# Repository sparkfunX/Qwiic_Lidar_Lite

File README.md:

SparkFun Qwiic LIDAR Lite v4
========================================

<table class="table table-hover table-striped table-bordered">
  <tr align="center">
   <td></td>
   <td></td>
  </tr>
  <tr align="center">
   <td><i>Qwiic LIDAR-Lite v4 [<a href="https://www.sparkfun.com/products/15777">SPX-15777</a>]</i></td>
   <td><i>Garmin LIDAR-Lite v4 LED - Distance Measurement Sensor [<a href="https://www.sparkfun.com/products/15776">SEN-15776</a>]</i></td>
  </tr>
</table>

Arduino library for GARMIN LIDAR Lite v4: high-performance optical distance sensing.

Repository Contents
-------------------

* **/examples** - Example sketches for the library (.ino). Run these from the Arduino IDE.
* **/src** - Source files for the library (.cpp, .h).
* **keywords.txt** - Keywords from this library that will be highlighted in the Arduino IDE. 
* **library.properties** - General library properties for the Arduino package manager. 

Documentation
--------------

* **[Installing an Arduino Library Guide](https://learn.sparkfun.com/tutorials/installing-an-arduino-library)** - Basic information on how to install an Arduino library.

License Information
-------------------

This product is _**open source**_!

Please review the LICENSE.md file for license information.

If you have any questions or concerns on licensing, please contact technical support on our [SparkFun forums](https://forum.sparkfun.com/viewforum.php?f=152).

Distributed as-is; no warranty is given.

- Your friends at SparkFun.

_<COLLABORATION CREDIT>_

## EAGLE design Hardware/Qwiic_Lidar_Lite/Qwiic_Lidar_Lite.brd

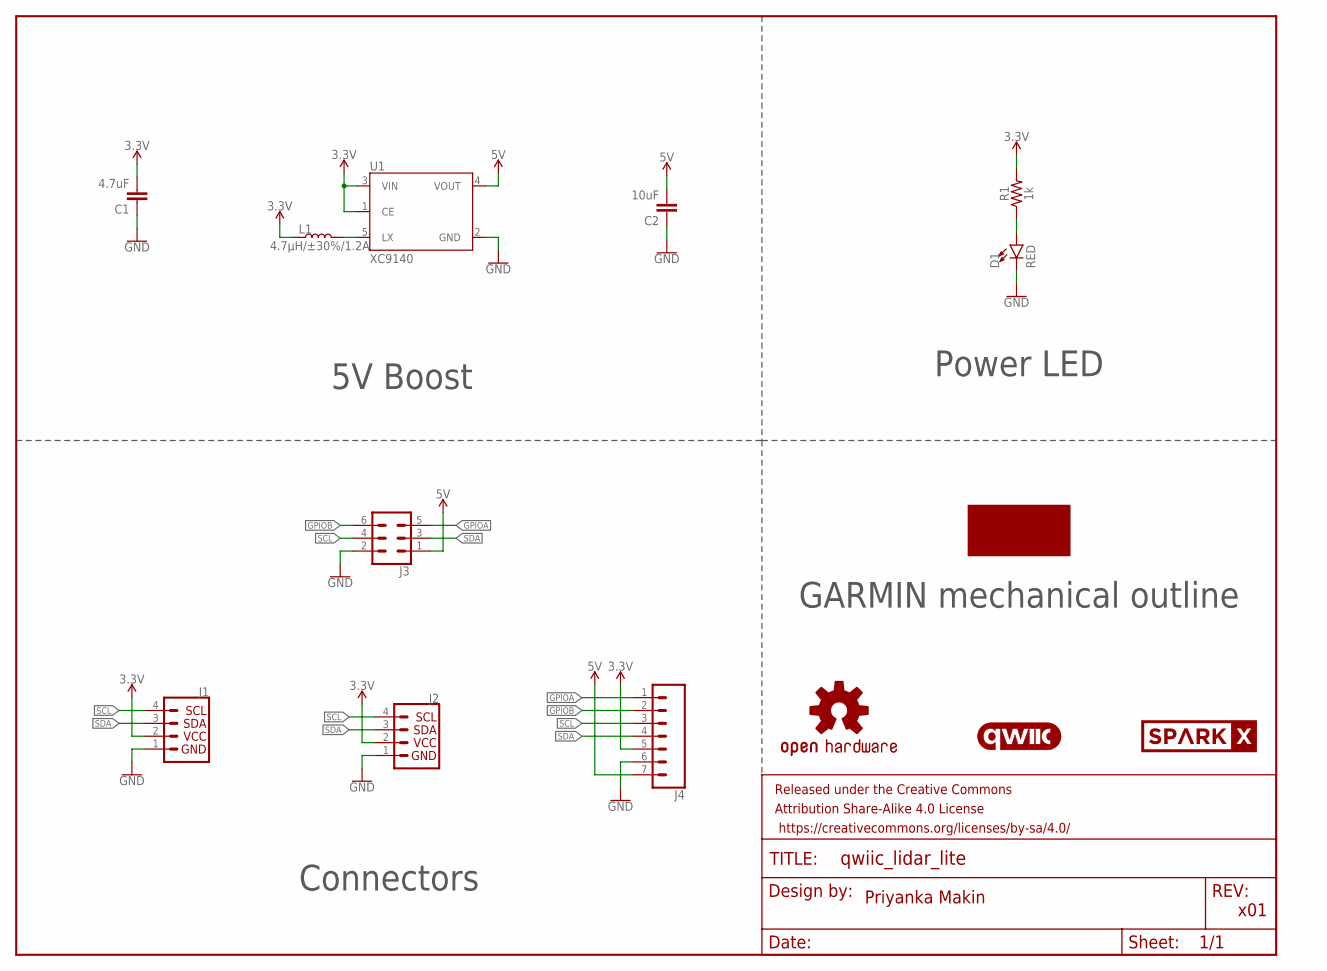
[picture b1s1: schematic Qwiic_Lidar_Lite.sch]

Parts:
C1: 4.7uF; 0603
C2: 10uF; 0603
D1: RED; LED-0603
FRAME1: FRAME-LETTER; CREATIVE_COMMONS
J1, J2: QWIIC_CONNECTORJS-1MM; JST04_1MM_RA
J3: CONN_03X22MM; CONN_3X2_2MM
J4: CONN_07NO_SILK; 1X07_NO_SILK
L1: 4.7µH/±30%/1.2A; INDUCTOR_4.7UH
LOGO1: QWIIC_LOGO_CONNECTOR; QWIIC_5.5MM
LOGO2: OSHW-LOGOMINI; OSHW-LOGO-MINI
R1: 1k; 0603
U1: XC9140; SOT23-5
U$7: LIDAR_LITE
U$8: SPARKX-LOGO4; SPARKX-MEDIUM

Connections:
3.3V: C1.2, J1.2, J2.2, J4.5, L1.P$1 (1), R1.2, U1.1 (CE), U1.3 (VIN)
5V: C2.2, J3.1, J4.7, U1.4 (VOUT)
GND: C1.1, C2.1, D1.C, J1.1, J2.1, J3.2, J4.6, U1.2 (GND)
GPIOA: J3.5, J4.1
GPIOB: J3.6, J4.2
unnamed: D1.A, R1.1
unnamed: L1.P$2 (2), U1.5 (LX)
SCL: J1.4, J2.4, J3.4, J4.3
SDA: J1.3, J2.3, J3.3, J4.4

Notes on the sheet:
Connectors
Priyanka Makin
x01
GARMIN mechanical outline
5V Boost
Power LED

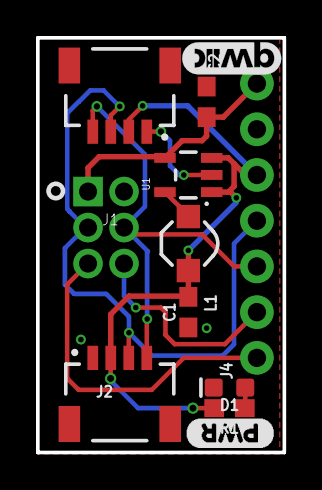
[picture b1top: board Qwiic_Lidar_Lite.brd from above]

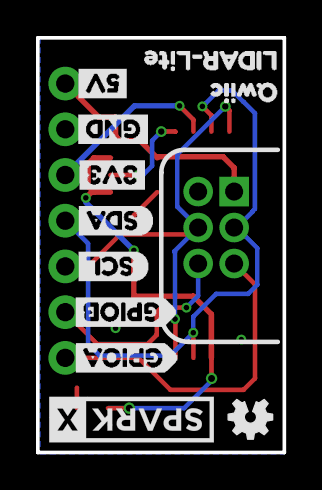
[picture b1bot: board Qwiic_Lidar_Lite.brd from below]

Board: 2 copper layers, 13.7 x 23.0 mm, 25 parts (13 on the bottom side), 9 nets.

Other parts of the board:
U$1: GND3
U$2: 3V30
U$3: GPIOA5
U$4: GPIOB2
U$5: SCL1
U$6: SDA4
U$9: QWIIC0
U$10: 5V0
U$11: LIDAR#LITE1
U$12: PWR0

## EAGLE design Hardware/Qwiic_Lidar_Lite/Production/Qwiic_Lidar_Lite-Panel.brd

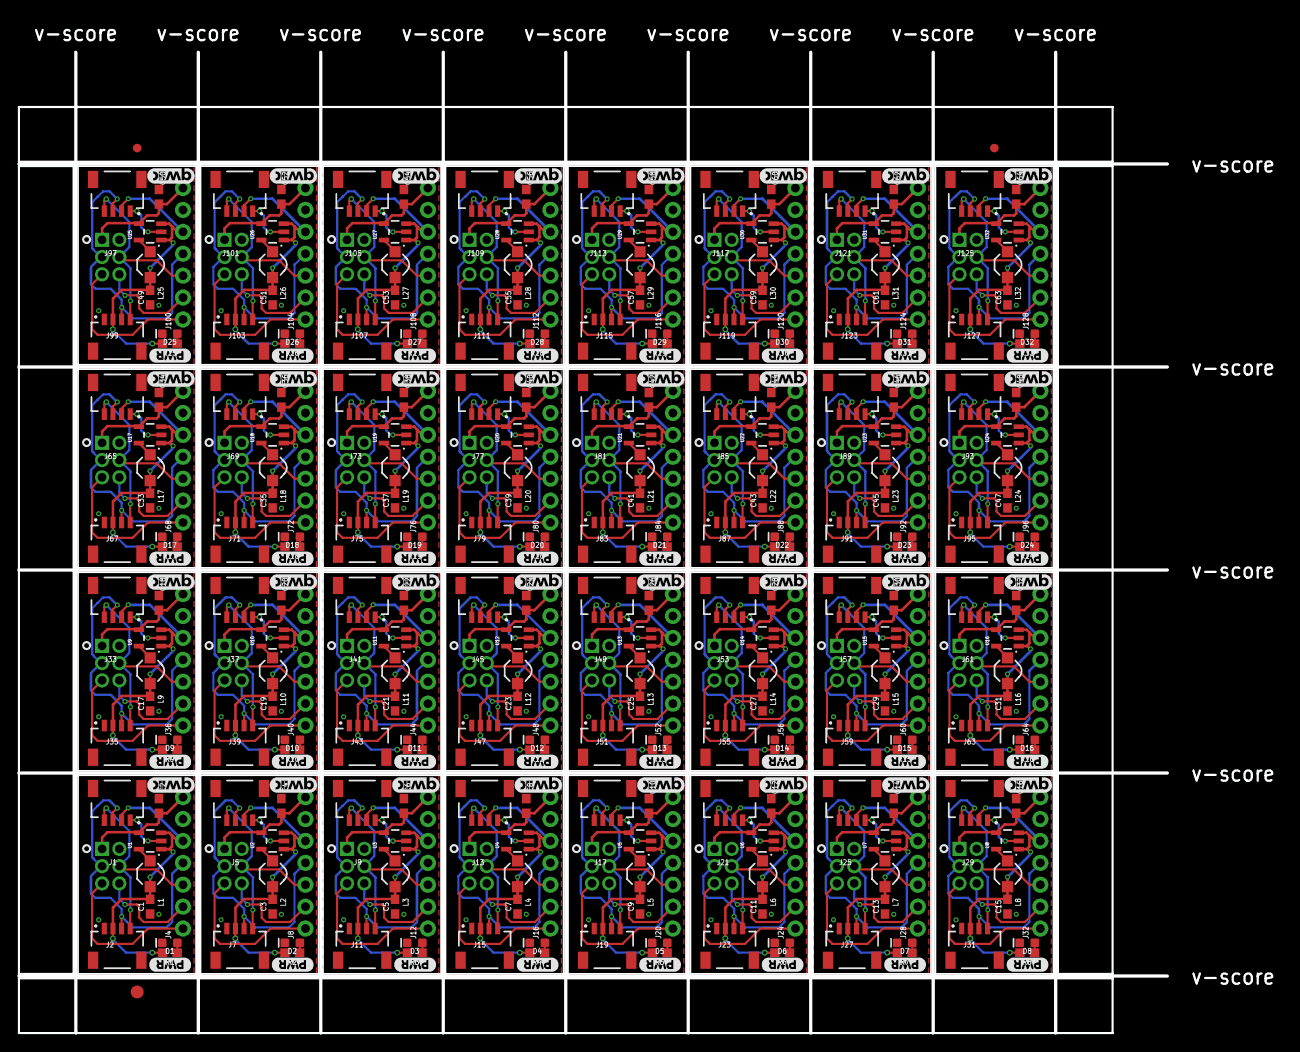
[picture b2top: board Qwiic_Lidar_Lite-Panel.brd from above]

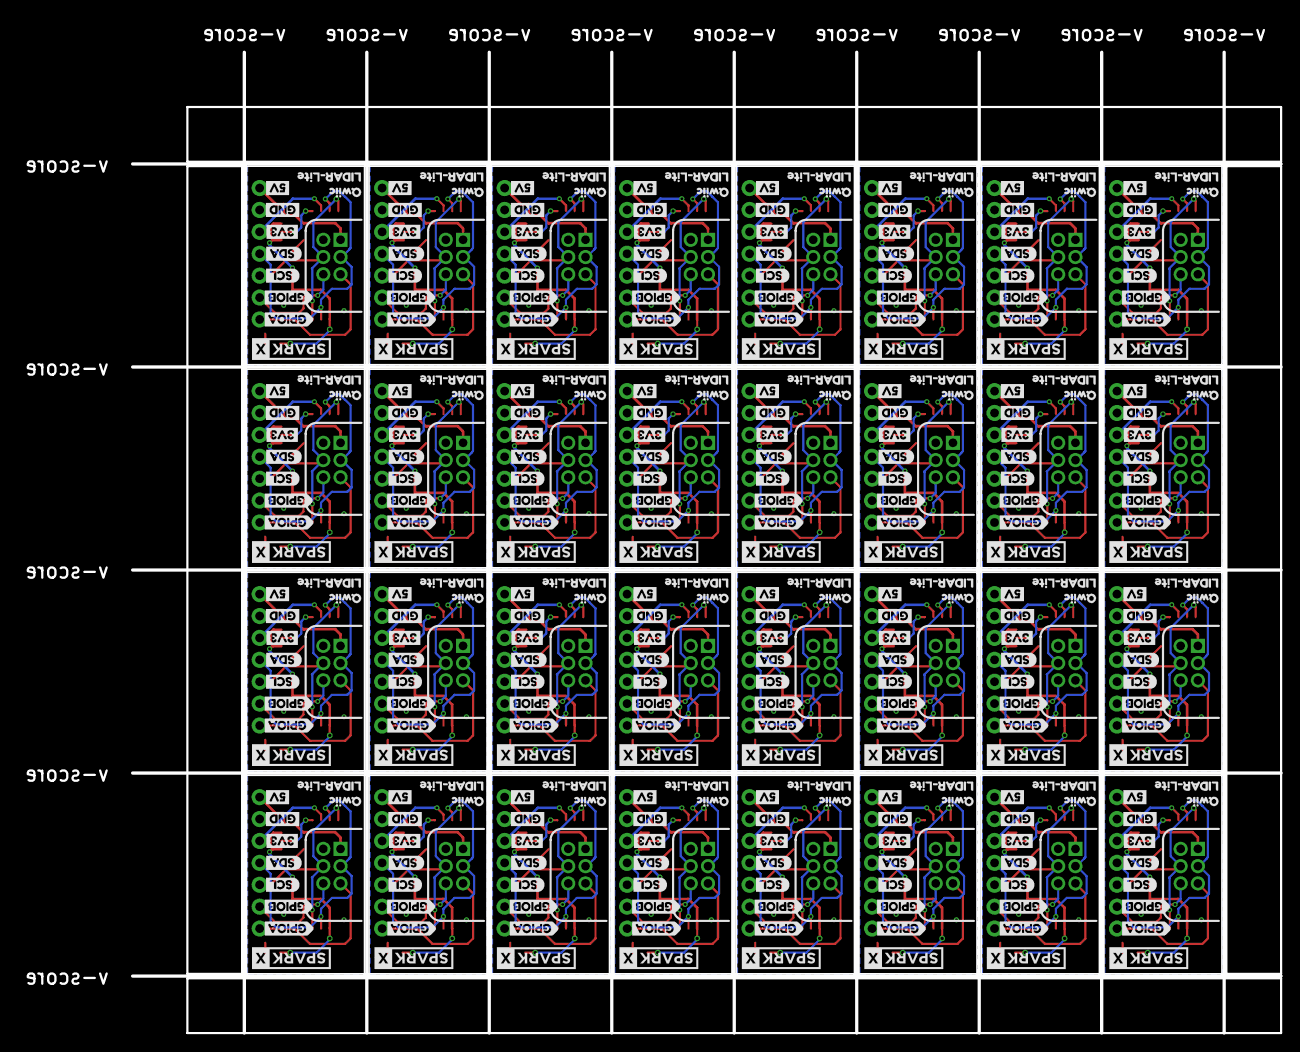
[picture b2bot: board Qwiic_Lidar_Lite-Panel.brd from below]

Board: 2 copper layers, 146.4 x 117.6 mm, 739 parts (384 on the bottom side), 288 nets.

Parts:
C1, C3, C5, C7, C9, C11, C13, C15, C17, C19, C21, C23, C25, C27, C29, C31, C33, C35, C37, C39, C41, C43, C45, C47, C49, C51, C53, C55, C57, C59, C61, C63: 4.7uF; 0603
C2, C4, C6, C8, C10, C12, C14, C16, C18, C20, C22, C24, C26, C28, C30, C32, C34, C36, C38, C40, C42, C44, C46, C48, C50, C52, C54, C56, C58, C60, C62, C64: 10uF; 0603
D1, D2, D3, D4, D5, D6, D7, D8, D9, D10, D11, D12, D13, D14, D15, D16, D17, D18, D19, D20, D21, D22, D23, D24, D25, D26, D27, D28, D29, D30, D31, D32: RED; LED-0603
E$1, E$2: FIDUCIAL-1X2
E$3: FIDUCIAL-1.5X3
J1, J2, J5, J7, J9, J11, J13, J15, J17, J19, J21, J23, J25, J27, J29, J31, J33, J35, J37, J39, J41, J43, J45, J47, J49, J51, J53, J55, J57, J59, J61, J63, J65, J67, J69, J71, J73, J75, J77, J79, J81, J83, J85, J87, J89, J91, J93, J95, J97, J99, J101, J103, J105, J107, J109, J111, J113, J115, J117, J119, J121, J123, J125, J127: JST04_1MM_RA
J3, J6, J10, J14, J18, J22, J26, J30, J34, J38, J42, J46, J50, J54, J58, J62, J66, J70, J74, J78, J82, J86, J90, J94, J98, J102, J106, J110, J114, J118, J122, J126: CONN_3X2_2MM
J4, J8, J12, J16, J20, J24, J28, J32, J36, J40, J44, J48, J52, J56, J60, J64, J68, J72, J76, J80, J84, J88, J92, J96, J100, J104, J108, J112, J116, J120, J124, J128: 1X07_NO_SILK
L1, L2, L3, L4, L5, L6, L7, L8, L9, L10, L11, L12, L13, L14, L15, L16, L17, L18, L19, L20, L21, L22, L23, L24, L25, L26, L27, L28, L29, L30, L31, L32: 4.7µH/±30%/1.2A; INDUCTOR_4.7UH
LOGO1, LOGO2, LOGO3, LOGO4, LOGO5, LOGO6, LOGO7, LOGO8, LOGO9, LOGO10, LOGO11, LOGO12, LOGO13, LOGO14, LOGO15, LOGO16, LOGO17, LOGO18, LOGO19, LOGO20, LOGO21, LOGO22, LOGO23, LOGO24, LOGO25, LOGO26, LOGO27, LOGO28, LOGO29, LOGO30, LOGO31, LOGO32: QWIIC_LOGO_CONNECTOR; QWIIC_5.5MM
R1, R2, R3, R4, R5, R6, R7, R8, R9, R10, R11, R12, R13, R14, R15, R16, R17, R18, R19, R20, R21, R22, R23, R24, R25, R26, R27, R28, R29, R30, R31, R32: 1k; 0603
U1, U2, U3, U4, U5, U6, U7, U8, U9, U10, U11, U12, U13, U14, U15, U16, U17, U18, U19, U20, U21, U22, U23, U24, U25, U26, U27, U28, U29, U30, U31, U32: XC9140; SOT23-5
U$1, U$14, U$26, U$38, U$50, U$62, U$74, U$86, U$98, U$110, U$122, U$134, U$146, U$158, U$170, U$182, U$194, U$206, U$218, U$230, U$242, U$254, U$266, U$278, U$290, U$302, U$314, U$326, U$338, U$350, U$362, U$374: GND3
U$2, U$15, U$27, U$39, U$51, U$63, U$75, U$87, U$99, U$111, U$123, U$135, U$147, U$159, U$171, U$183, U$195, U$207, U$219, U$231, U$243, U$255, U$267, U$279, U$291, U$303, U$315, U$327, U$339, U$351, U$363, U$375: 3V30
U$3, U$21, U$33, U$45, U$57, U$69, U$81, U$93, U$105, U$117, U$129, U$141, U$153, U$165, U$177, U$189, U$201, U$213, U$225, U$237, U$249, U$261, U$273, U$285, U$297, U$309, U$321, U$333, U$345, U$357, U$369, U$381: GPIOA5
U$4, U$17, U$29, U$41, U$53, U$65, U$77, U$89, U$101, U$113, U$125, U$137, U$149, U$161, U$173, U$185, U$197, U$209, U$221, U$233, U$245, U$257, U$269, U$281, U$293, U$305, U$317, U$329, U$341, U$353, U$365, U$377: GPIOB2
U$5, U$18, U$30, U$42, U$54, U$66, U$78, U$90, U$102, U$114, U$126, U$138, U$150, U$162, U$174, U$186, U$198, U$210, U$222, U$234, U$246, U$258, U$270, U$282, U$294, U$306, U$318, U$330, U$342, U$354, U$366, U$378: SCL1
U$6, U$19, U$31, U$43, U$55, U$67, U$79, U$91, U$103, U$115, U$127, U$139, U$151, U$163, U$175, U$187, U$199, U$211, U$223, U$235, U$247, U$259, U$271, U$283, U$295, U$307, U$319, U$331, U$343, U$355, U$367, U$379: SDA4
U$7, U$13, U$25, U$37, U$49, U$61, U$73, U$85, U$97, U$109, U$121, U$133, U$145, U$157, U$169, U$181, U$193, U$205, U$217, U$229, U$241, U$253, U$265, U$277, U$289, U$301, U$313, U$325, U$337, U$349, U$361, U$373: LIDAR_LITE
U$8, U$16, U$28, U$40, U$52, U$64, U$76, U$88, U$100, U$112, U$124, U$136, U$148, U$160, U$172, U$184, U$196, U$208, U$220, U$232, U$244, U$256, U$268, U$280, U$292, U$304, U$316, U$328, U$340, U$352, U$364, U$376: SPARKX-LOGO4; SPARKX-MEDIUM
U$9, U$22, U$34, U$46, U$58, U$70, U$82, U$94, U$106, U$118, U$130, U$142, U$154, U$166, U$178, U$190, U$202, U$214, U$226, U$238, U$250, U$262, U$274, U$286, U$298, U$310, U$322, U$334, U$346, U$358, U$370, U$382: QWIIC0
U$10, U$20, U$32, U$44, U$56, U$68, U$80, U$92, U$104, U$116, U$128, U$140, U$152, U$164, U$176, U$188, U$200, U$212, U$224, U$236, U$248, U$260, U$272, U$284, U$296, U$308, U$320, U$332, U$344, U$356, U$368, U$380: 5V0
U$11, U$23, U$35, U$47, U$59, U$71, U$83, U$95, U$107, U$119, U$131, U$143, U$155, U$167, U$179, U$191, U$203, U$215, U$227, U$239, U$251, U$263, U$275, U$287, U$299, U$311, U$323, U$335, U$347, U$359, U$371, U$383: LIDAR#LITE1
U$12, U$24, U$36, U$48, U$60, U$72, U$84, U$96, U$108, U$120, U$132, U$144, U$156, U$168, U$180, U$192, U$204, U$216, U$228, U$240, U$252, U$264, U$276, U$288, U$300, U$312, U$324, U$336, U$348, U$360, U$372, U$384: PWR0

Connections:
3.3V: C1.2, J1.2, J2.2, J4.5, L1.P$1, R1.2, U1.1, U1.3
3.3V1: C3.2, J5.2, J7.2, J8.5, L2.P$1, R2.2, U2.1, U2.3
3.3V2: C5.2, J9.2, J11.2, J12.5, L3.P$1, R3.2, U3.1, U3.3
3.3V3: C7.2, J13.2, J15.2, J16.5, L4.P$1, R4.2, U4.1, U4.3
3.3V4: C9.2, J17.2, J19.2, J20.5, L5.P$1, R5.2, U5.1, U5.3
3.3V5: C11.2, J21.2, J23.2, J24.5, L6.P$1, R6.2, U6.1, U6.3
3.3V6: C13.2, J25.2, J27.2, J28.5, L7.P$1, R7.2, U7.1, U7.3
3.3V7: C15.2, J29.2, J31.2, J32.5, L8.P$1, R8.2, U8.1, U8.3
3.3V8: C17.2, J33.2, J35.2, J36.5, L9.P$1, R9.2, U9.1, U9.3
3.3V9: C19.2, J37.2, J39.2, J40.5, L10.P$1, R10.2, U10.1, U10.3
3.3V10: C21.2, J41.2, J43.2, J44.5, L11.P$1, R11.2, U11.1, U11.3
3.3V11: C23.2, J45.2, J47.2, J48.5, L12.P$1, R12.2, U12.1, U12.3
3.3V12: C25.2, J49.2, J51.2, J52.5, L13.P$1, R13.2, U13.1, U13.3
3.3V13: C27.2, J53.2, J55.2, J56.5, L14.P$1, R14.2, U14.1, U14.3
3.3V14: C29.2, J57.2, J59.2, J60.5, L15.P$1, R15.2, U15.1, U15.3
3.3V15: C31.2, J61.2, J63.2, J64.5, L16.P$1, R16.2, U16.1, U16.3
3.3V16: C33.2, J65.2, J67.2, J68.5, L17.P$1, R17.2, U17.1, U17.3
3.3V17: C35.2, J69.2, J71.2, J72.5, L18.P$1, R18.2, U18.1, U18.3
3.3V18: C37.2, J73.2, J75.2, J76.5, L19.P$1, R19.2, U19.1, U19.3
3.3V19: C39.2, J77.2, J79.2, J80.5, L20.P$1, R20.2, U20.1, U20.3
3.3V20: C41.2, J81.2, J83.2, J84.5, L21.P$1, R21.2, U21.1, U21.3
3.3V21: C43.2, J85.2, J87.2, J88.5, L22.P$1, R22.2, U22.1, U22.3
3.3V22: C45.2, J89.2, J91.2, J92.5, L23.P$1, R23.2, U23.1, U23.3
3.3V23: C47.2, J93.2, J95.2, J96.5, L24.P$1, R24.2, U24.1, U24.3
3.3V24: C49.2, J97.2, J99.2, J100.5, L25.P$1, R25.2, U25.1, U25.3
3.3V25: C51.2, J101.2, J103.2, J104.5, L26.P$1, R26.2, U26.1, U26.3
3.3V26: C53.2, J105.2, J107.2, J108.5, L27.P$1, R27.2, U27.1, U27.3
3.3V27: C55.2, J109.2, J111.2, J112.5, L28.P$1, R28.2, U28.1, U28.3
3.3V28: C57.2, J113.2, J115.2, J116.5, L29.P$1, R29.2, U29.1, U29.3
3.3V29: C59.2, J117.2, J119.2, J120.5, L30.P$1, R30.2, U30.1, U30.3
3.3V30: C61.2, J121.2, J123.2, J124.5, L31.P$1, R31.2, U31.1, U31.3
3.3V31: C63.2, J125.2, J127.2, J128.5, L32.P$1, R32.2, U32.1, U32.3
5V: C2.2, J3.1, J4.7, U1.4
5V1: C4.2, J6.1, J8.7, U2.4
5V2: C6.2, J10.1, J12.7, U3.4
5V3: C8.2, J14.1, J16.7, U4.4
5V4: C10.2, J18.1, J20.7, U5.4
5V5: C12.2, J22.1, J24.7, U6.4
5V6: C14.2, J26.1, J28.7, U7.4
5V7: C16.2, J30.1, J32.7, U8.4
5V8: C18.2, J34.1, J36.7, U9.4
5V9: C20.2, J38.1, J40.7, U10.4
5V10: C22.2, J42.1, J44.7, U11.4
5V11: C24.2, J46.1, J48.7, U12.4
5V12: C26.2, J50.1, J52.7, U13.4
5V13: C28.2, J54.1, J56.7, U14.4
5V14: C30.2, J58.1, J60.7, U15.4
5V15: C32.2, J62.1, J64.7, U16.4
5V16: C34.2, J66.1, J68.7, U17.4
5V17: C36.2, J70.1, J72.7, U18.4
5V18: C38.2, J74.1, J76.7, U19.4
5V19: C40.2, J78.1, J80.7, U20.4
5V20: C42.2, J82.1, J84.7, U21.4
5V21: C44.2, J86.1, J88.7, U22.4
5V22: C46.2, J90.1, J92.7, U23.4
5V23: C48.2, J94.1, J96.7, U24.4
5V24: C50.2, J98.1, J100.7, U25.4
5V25: C52.2, J102.1, J104.7, U26.4
5V26: C54.2, J106.1, J108.7, U27.4
5V27: C56.2, J110.1, J112.7, U28.4
5V28: C58.2, J114.1, J116.7, U29.4
5V29: C60.2, J118.1, J120.7, U30.4
5V30: C62.2, J122.1, J124.7, U31.4
5V31: C64.2, J126.1, J128.7, U32.4
GND: C1.1, C2.1, D1.C, J1.1, J2.1, J3.2, J4.6, U1.2
GND1: C3.1, C4.1, D2.C, J5.1, J6.2, J7.1, J8.6, U2.2
GND2: C5.1, C6.1, D3.C, J9.1, J10.2, J11.1, J12.6, U3.2
GND3: C7.1, C8.1, D4.C, J13.1, J14.2, J15.1, J16.6, U4.2
GND4: C9.1, C10.1, D5.C, J17.1, J18.2, J19.1, J20.6, U5.2
GND5: C11.1, C12.1, D6.C, J21.1, J22.2, J23.1, J24.6, U6.2
GND6: C13.1, C14.1, D7.C, J25.1, J26.2, J27.1, J28.6, U7.2
GND7: C15.1, C16.1, D8.C, J29.1, J30.2, J31.1, J32.6, U8.2
GND8: C17.1, C18.1, D9.C, J33.1, J34.2, J35.1, J36.6, U9.2
GND9: C19.1, C20.1, D10.C, J37.1, J38.2, J39.1, J40.6, U10.2
GND10: C21.1, C22.1, D11.C, J41.1, J42.2, J43.1, J44.6, U11.2
GND11: C23.1, C24.1, D12.C, J45.1, J46.2, J47.1, J48.6, U12.2
GND12: C25.1, C26.1, D13.C, J49.1, J50.2, J51.1, J52.6, U13.2
GND13: C27.1, C28.1, D14.C, J53.1, J54.2, J55.1, J56.6, U14.2
GND14: C29.1, C30.1, D15.C, J57.1, J58.2, J59.1, J60.6, U15.2
GND15: C31.1, C32.1, D16.C, J61.1, J62.2, J63.1, J64.6, U16.2
GND16: C33.1, C34.1, D17.C, J65.1, J66.2, J67.1, J68.6, U17.2
GND17: C35.1, C36.1, D18.C, J69.1, J70.2, J71.1, J72.6, U18.2
GND18: C37.1, C38.1, D19.C, J73.1, J74.2, J75.1, J76.6, U19.2
GND19: C39.1, C40.1, D20.C, J77.1, J78.2, J79.1, J80.6, U20.2
GND20: C41.1, C42.1, D21.C, J81.1, J82.2, J83.1, J84.6, U21.2
GND21: C43.1, C44.1, D22.C, J85.1, J86.2, J87.1, J88.6, U22.2
GND22: C45.1, C46.1, D23.C, J89.1, J90.2, J91.1, J92.6, U23.2
GND23: C47.1, C48.1, D24.C, J93.1, J94.2, J95.1, J96.6, U24.2
GND24: C49.1, C50.1, D25.C, J97.1, J98.2, J99.1, J100.6, U25.2
GND25: C51.1, C52.1, D26.C, J101.1, J102.2, J103.1, J104.6, U26.2
GND26: C53.1, C54.1, D27.C, J105.1, J106.2, J107.1, J108.6, U27.2
GND27: C55.1, C56.1, D28.C, J109.1, J110.2, J111.1, J112.6, U28.2
GND28: C57.1, C58.1, D29.C, J113.1, J114.2, J115.1, J116.6, U29.2
GND29: C59.1, C60.1, D30.C, J117.1, J118.2, J119.1, J120.6, U30.2
GND30: C61.1, C62.1, D31.C, J121.1, J122.2, J123.1, J124.6, U31.2
GND31: C63.1, C64.1, D32.C, J125.1, J126.2, J127.1, J128.6, U32.2
GPIOA: J3.5, J4.1
GPIOA1: J6.5, J8.1
GPIOA2: J10.5, J12.1
GPIOA3: J14.5, J16.1
GPIOA4: J18.5, J20.1
GPIOA5: J22.5, J24.1
GPIOA6: J26.5, J28.1
GPIOA7: J30.5, J32.1
GPIOA8: J34.5, J36.1
GPIOA9: J38.5, J40.1
GPIOA10: J42.5, J44.1
GPIOA11: J46.5, J48.1
GPIOA12: J50.5, J52.1
GPIOA13: J54.5, J56.1
GPIOA14: J58.5, J60.1
GPIOA15: J62.5, J64.1
GPIOA16: J66.5, J68.1
GPIOA17: J70.5, J72.1
GPIOA18: J74.5, J76.1
GPIOA19: J78.5, J80.1
GPIOA20: J82.5, J84.1
GPIOA21: J86.5, J88.1
GPIOA22: J90.5, J92.1
GPIOA23: J94.5, J96.1
GPIOA24: J98.5, J100.1
GPIOA25: J102.5, J104.1
GPIOA26: J106.5, J108.1
GPIOA27: J110.5, J112.1
GPIOA28: J114.5, J116.1
GPIOA29: J118.5, J120.1
GPIOA30: J122.5, J124.1
GPIOA31: J126.5, J128.1
GPIOB: J3.6, J4.2
GPIOB1: J6.6, J8.2
GPIOB2: J10.6, J12.2
GPIOB3: J14.6, J16.2
GPIOB4: J18.6, J20.2
GPIOB5: J22.6, J24.2
GPIOB6: J26.6, J28.2
GPIOB7: J30.6, J32.2
GPIOB8: J34.6, J36.2
GPIOB9: J38.6, J40.2
GPIOB10: J42.6, J44.2
GPIOB11: J46.6, J48.2
GPIOB12: J50.6, J52.2
GPIOB13: J54.6, J56.2
GPIOB14: J58.6, J60.2
GPIOB15: J62.6, J64.2
GPIOB16: J66.6, J68.2
GPIOB17: J70.6, J72.2
GPIOB18: J74.6, J76.2
GPIOB19: J78.6, J80.2
GPIOB20: J82.6, J84.2
GPIOB21: J86.6, J88.2
GPIOB22: J90.6, J92.2
GPIOB23: J94.6, J96.2
GPIOB24: J98.6, J100.2
GPIOB25: J102.6, J104.2
GPIOB26: J106.6, J108.2
GPIOB27: J110.6, J112.2
GPIOB28: J114.6, J116.2
GPIOB29: J118.6, J120.2
GPIOB30: J122.6, J124.2
GPIOB31: J126.6, J128.2
unnamed: D1.A, R1.1
unnamed: L1.P$2, U1.5
unnamed: L2.P$2, U2.5
unnamed: D2.A, R2.1
unnamed: L3.P$2, U3.5
unnamed: D3.A, R3.1
unnamed: L4.P$2, U4.5
unnamed: D4.A, R4.1
unnamed: L5.P$2, U5.5
unnamed: D5.A, R5.1
unnamed: L6.P$2, U6.5
unnamed: D6.A, R6.1
unnamed: L7.P$2, U7.5
unnamed: D7.A, R7.1
unnamed: L8.P$2, U8.5
unnamed: D8.A, R8.1
unnamed: L9.P$2, U9.5
unnamed: D9.A, R9.1
unnamed: L10.P$2, U10.5
unnamed: D10.A, R10.1
unnamed: L11.P$2, U11.5
unnamed: D11.A, R11.1
unnamed: L12.P$2, U12.5
unnamed: D12.A, R12.1
unnamed: L13.P$2, U13.5
unnamed: D13.A, R13.1
unnamed: L14.P$2, U14.5
unnamed: D14.A, R14.1
unnamed: L15.P$2, U15.5
unnamed: D15.A, R15.1
unnamed: L16.P$2, U16.5
unnamed: D16.A, R16.1
unnamed: L17.P$2, U17.5
unnamed: D17.A, R17.1
unnamed: L18.P$2, U18.5
unnamed: D18.A, R18.1
unnamed: L19.P$2, U19.5
unnamed: D19.A, R19.1
unnamed: L20.P$2, U20.5
unnamed: D20.A, R20.1
unnamed: L21.P$2, U21.5
unnamed: D21.A, R21.1
unnamed: L22.P$2, U22.5
unnamed: D22.A, R22.1
unnamed: L23.P$2, U23.5
unnamed: D23.A, R23.1
unnamed: L24.P$2, U24.5
unnamed: D24.A, R24.1
unnamed: L25.P$2, U25.5
unnamed: D25.A, R25.1
unnamed: L26.P$2, U26.5
unnamed: D26.A, R26.1
unnamed: L27.P$2, U27.5
unnamed: D27.A, R27.1
unnamed: L28.P$2, U28.5
unnamed: D28.A, R28.1
unnamed: L29.P$2, U29.5
unnamed: D29.A, R29.1
unnamed: L30.P$2, U30.5
unnamed: D30.A, R30.1
unnamed: L31.P$2, U31.5
unnamed: D31.A, R31.1
unnamed: L32.P$2, U32.5
unnamed: D32.A, R32.1
SCL: J1.4, J2.4, J3.4, J4.3
SCL1: J5.4, J6.4, J7.4, J8.3
SCL2: J9.4, J10.4, J11.4, J12.3
SCL3: J13.4, J14.4, J15.4, J16.3
SCL4: J17.4, J18.4, J19.4, J20.3
SCL5: J21.4, J22.4, J23.4, J24.3
SCL6: J25.4, J26.4, J27.4, J28.3
SCL7: J29.4, J30.4, J31.4, J32.3
SCL8: J33.4, J34.4, J35.4, J36.3
SCL9: J37.4, J38.4, J39.4, J40.3
SCL10: J41.4, J42.4, J43.4, J44.3
SCL11: J45.4, J46.4, J47.4, J48.3
SCL12: J49.4, J50.4, J51.4, J52.3
SCL13: J53.4, J54.4, J55.4, J56.3
SCL14: J57.4, J58.4, J59.4, J60.3
SCL15: J61.4, J62.4, J63.4, J64.3
SCL16: J65.4, J66.4, J67.4, J68.3
SCL17: J69.4, J70.4, J71.4, J72.3
SCL18: J73.4, J74.4, J75.4, J76.3
SCL19: J77.4, J78.4, J79.4, J80.3
SCL20: J81.4, J82.4, J83.4, J84.3
SCL21: J85.4, J86.4, J87.4, J88.3
SCL22: J89.4, J90.4, J91.4, J92.3
SCL23: J93.4, J94.4, J95.4, J96.3
SCL24: J97.4, J98.4, J99.4, J100.3
SCL25: J101.4, J102.4, J103.4, J104.3
SCL26: J105.4, J106.4, J107.4, J108.3
SCL27: J109.4, J110.4, J111.4, J112.3
SCL28: J113.4, J114.4, J115.4, J116.3
SCL29: J117.4, J118.4, J119.4, J120.3
SCL30: J121.4, J122.4, J123.4, J124.3
SCL31: J125.4, J126.4, J127.4, J128.3
SDA: J1.3, J2.3, J3.3, J4.4
SDA1: J5.3, J6.3, J7.3, J8.4
SDA2: J9.3, J10.3, J11.3, J12.4
SDA3: J13.3, J14.3, J15.3, J16.4
SDA4: J17.3, J18.3, J19.3, J20.4
SDA5: J21.3, J22.3, J23.3, J24.4
SDA6: J25.3, J26.3, J27.3, J28.4
SDA7: J29.3, J30.3, J31.3, J32.4
SDA8: J33.3, J34.3, J35.3, J36.4
SDA9: J37.3, J38.3, J39.3, J40.4
SDA10: J41.3, J42.3, J43.3, J44.4
SDA11: J45.3, J46.3, J47.3, J48.4
SDA12: J49.3, J50.3, J51.3, J52.4
SDA13: J53.3, J54.3, J55.3, J56.4
SDA14: J57.3, J58.3, J59.3, J60.4
SDA15: J61.3, J62.3, J63.3, J64.4
SDA16: J65.3, J66.3, J67.3, J68.4
SDA17: J69.3, J70.3, J71.3, J72.4
SDA18: J73.3, J74.3, J75.3, J76.4
SDA19: J77.3, J78.3, J79.3, J80.4
SDA20: J81.3, J82.3, J83.3, J84.4
SDA21: J85.3, J86.3, J87.3, J88.4
SDA22: J89.3, J90.3, J91.3, J92.4
SDA23: J93.3, J94.3, J95.3, J96.4
SDA24: J97.3, J98.3, J99.3, J100.4
SDA25: J101.3, J102.3, J103.3, J104.4
SDA26: J105.3, J106.3, J107.3, J108.4
SDA27: J109.3, J110.3, J111.3, J112.4
SDA28: J113.3, J114.3, J115.3, J116.4
SDA29: J117.3, J118.3, J119.3, J120.4
SDA30: J121.3, J122.3, J123.3, J124.4
SDA31: J125.3, J126.3, J127.3, J128.4

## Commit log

2019-09-17 Board design finished
    Finished designing schematic/board in Eagle. Created production output files
2019-09-17 Removed weird eagle files
2019-09-20 Updated board design with power LED
2019-10-28 Stuff and things

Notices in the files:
parts and their libraries:
SparkFun-Capacitors: Licensing: Creative Commons ShareAlike 4.0 International - https://creativecommons.org/licenses/by-sa/4.0
SparkFun-Aesthetics: Released under the Creative Commons Attribution Share-Alike 4.0 License
SparkFun-Aesthetics: https://creativecommons.org/licenses/by-sa/4.0
